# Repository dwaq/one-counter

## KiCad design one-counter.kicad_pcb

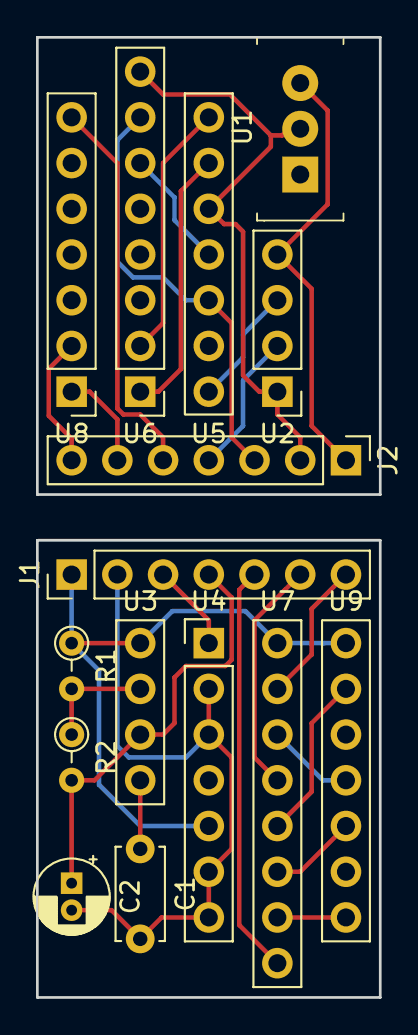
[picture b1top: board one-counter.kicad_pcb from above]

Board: 2 copper layers, 19.1 x 53.3 mm, 15 parts (0 on the bottom side), 22 nets.

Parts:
C1: 0.01uF; C_Disc_D5.0mm_W2.5mm_P5.00mm
C2: 2.2uF; CP_Radial_D4.0mm_P1.50mm
J1: Conn_01x07-L; PinHeader_1x07_P2.54mm_Vertical
J2: Conn_01x07-R; PinHeader_1x07_P2.54mm_Vertical
R1: 1k; R_Axial_DIN0204_L3.6mm_D1.6mm_P2.54mm_Vertical
R2: 330k; R_Axial_DIN0204_L3.6mm_D1.6mm_P2.54mm_Vertical
U1: L7805; TO-220-3
U2: 555-L; Pin_Header_Straight_1x04_Pitch2.54mm
U3: 555-R; Pin_Header_Straight_1x04_Pitch2.54mm_Right
U4: 74LS90-L; Pin_Header_Straight_1x07_Pitch2.54mm
U5: 74LS90-R; Pin_Header_Straight_1x07_Pitch2.54mm_Right
U6: 7447-L; Pin_Header_Straight_1x08_Pitch2.54mm
U7: 7447-R; Pin_Header_Straight_1x08_Pitch2.54mm_Right
U8: 5082-7650-L; Pin_Header_Straight_1x07_Pitch2.54mm
U9: 5082-7650-R; Pin_Header_Straight_1x07_Pitch2.54mm_Right

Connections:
+5V: J1.1, J2.1, R1.1, U1.3, U2.4, U3.8, U4.5, U7.16, U9.14
/1Hz: U2.3, U5.14
GND: C1.2, C2.2, J1.2, J2.2, U1.2, U2.1, U4.2, U4.3, U4.6, U4.7, U5.10, U6.8
unnamed: C1.1, U3.5
unnamed: R1.2, R2.1, U3.7
unnamed: U5.8, U6.2
unnamed: U5.9, U6.1
unnamed: U5.11, U6.6
unnamed: U7.10, U9.8
unnamed: U7.11, U9.10
unnamed: U7.12, U9.13
unnamed: U7.14, U9.11
U2-2: J2.4, U2.2
U3-6: C2.1, J1.4, R2.2, U3.6
U4-1: J1.3, U4.1
U5-12: J2.3, U5.12, U6.7
U7-9: J1.5, U7.9
U7-13: J1.6, U7.13
U7-15: J1.7, U7.15
U8-1: J2.6, U8.1
U8-2: J2.7, U8.2
U8-7: J2.5, U8.7

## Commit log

2018-09-13 Design some of the schematic
    Parts:
    7805
    555
    74ls90
    7447
    7 seg - 5082-7650
2018-09-13 design 555 for 1Hz operation
2018-09-13 move 555 circuit closer
2018-09-13 associate symbols and add pullup to power on 7447
2018-09-13 add power flags
2018-09-13 applied physical footprints
2018-09-13 generate netlist
2018-09-13 update netlist
2018-09-13 make 555 and 74LS90 symbols
2018-09-13 add 7447 to library
2018-09-13 make display symbol
2018-09-13 use new 555 in sch
2018-09-13 redo schematic with custom parts
2018-09-13 annotate symbols
2018-09-13 assign 2.54mm headers to all parts
2018-09-13 create new footprint library for right side
2018-09-13 Add right side parts to layout
2018-09-13 board laid out except 10 tracks
2018-09-13 routing is possible
2018-09-13 don't need resistor
2018-09-13 Run ERC/DRC and remove one anode connection
2018-09-14 Change from 8 to 7 pin header
2018-09-14 changed resistor size
2018-09-14 move top components into place
2018-09-14 bottom footprints mostly in place
2018-09-14 move all components into place
2018-09-14 flip connector on top half
2018-09-14 route bottom half
2018-09-14 add board outlines
2018-09-14 Add design rules, increase track width to 10 mils, change tracks' layers
2018-09-14 remove front silkscreen for manufactor
2018-09-14 send gerbers to oshpark
2018-09-14 remove broken/unused files
2018-09-14 add more file types to gitignore
2018-09-14 remove now-ignored backup and netlist
2018-09-14 use link to project instead of absolute path
